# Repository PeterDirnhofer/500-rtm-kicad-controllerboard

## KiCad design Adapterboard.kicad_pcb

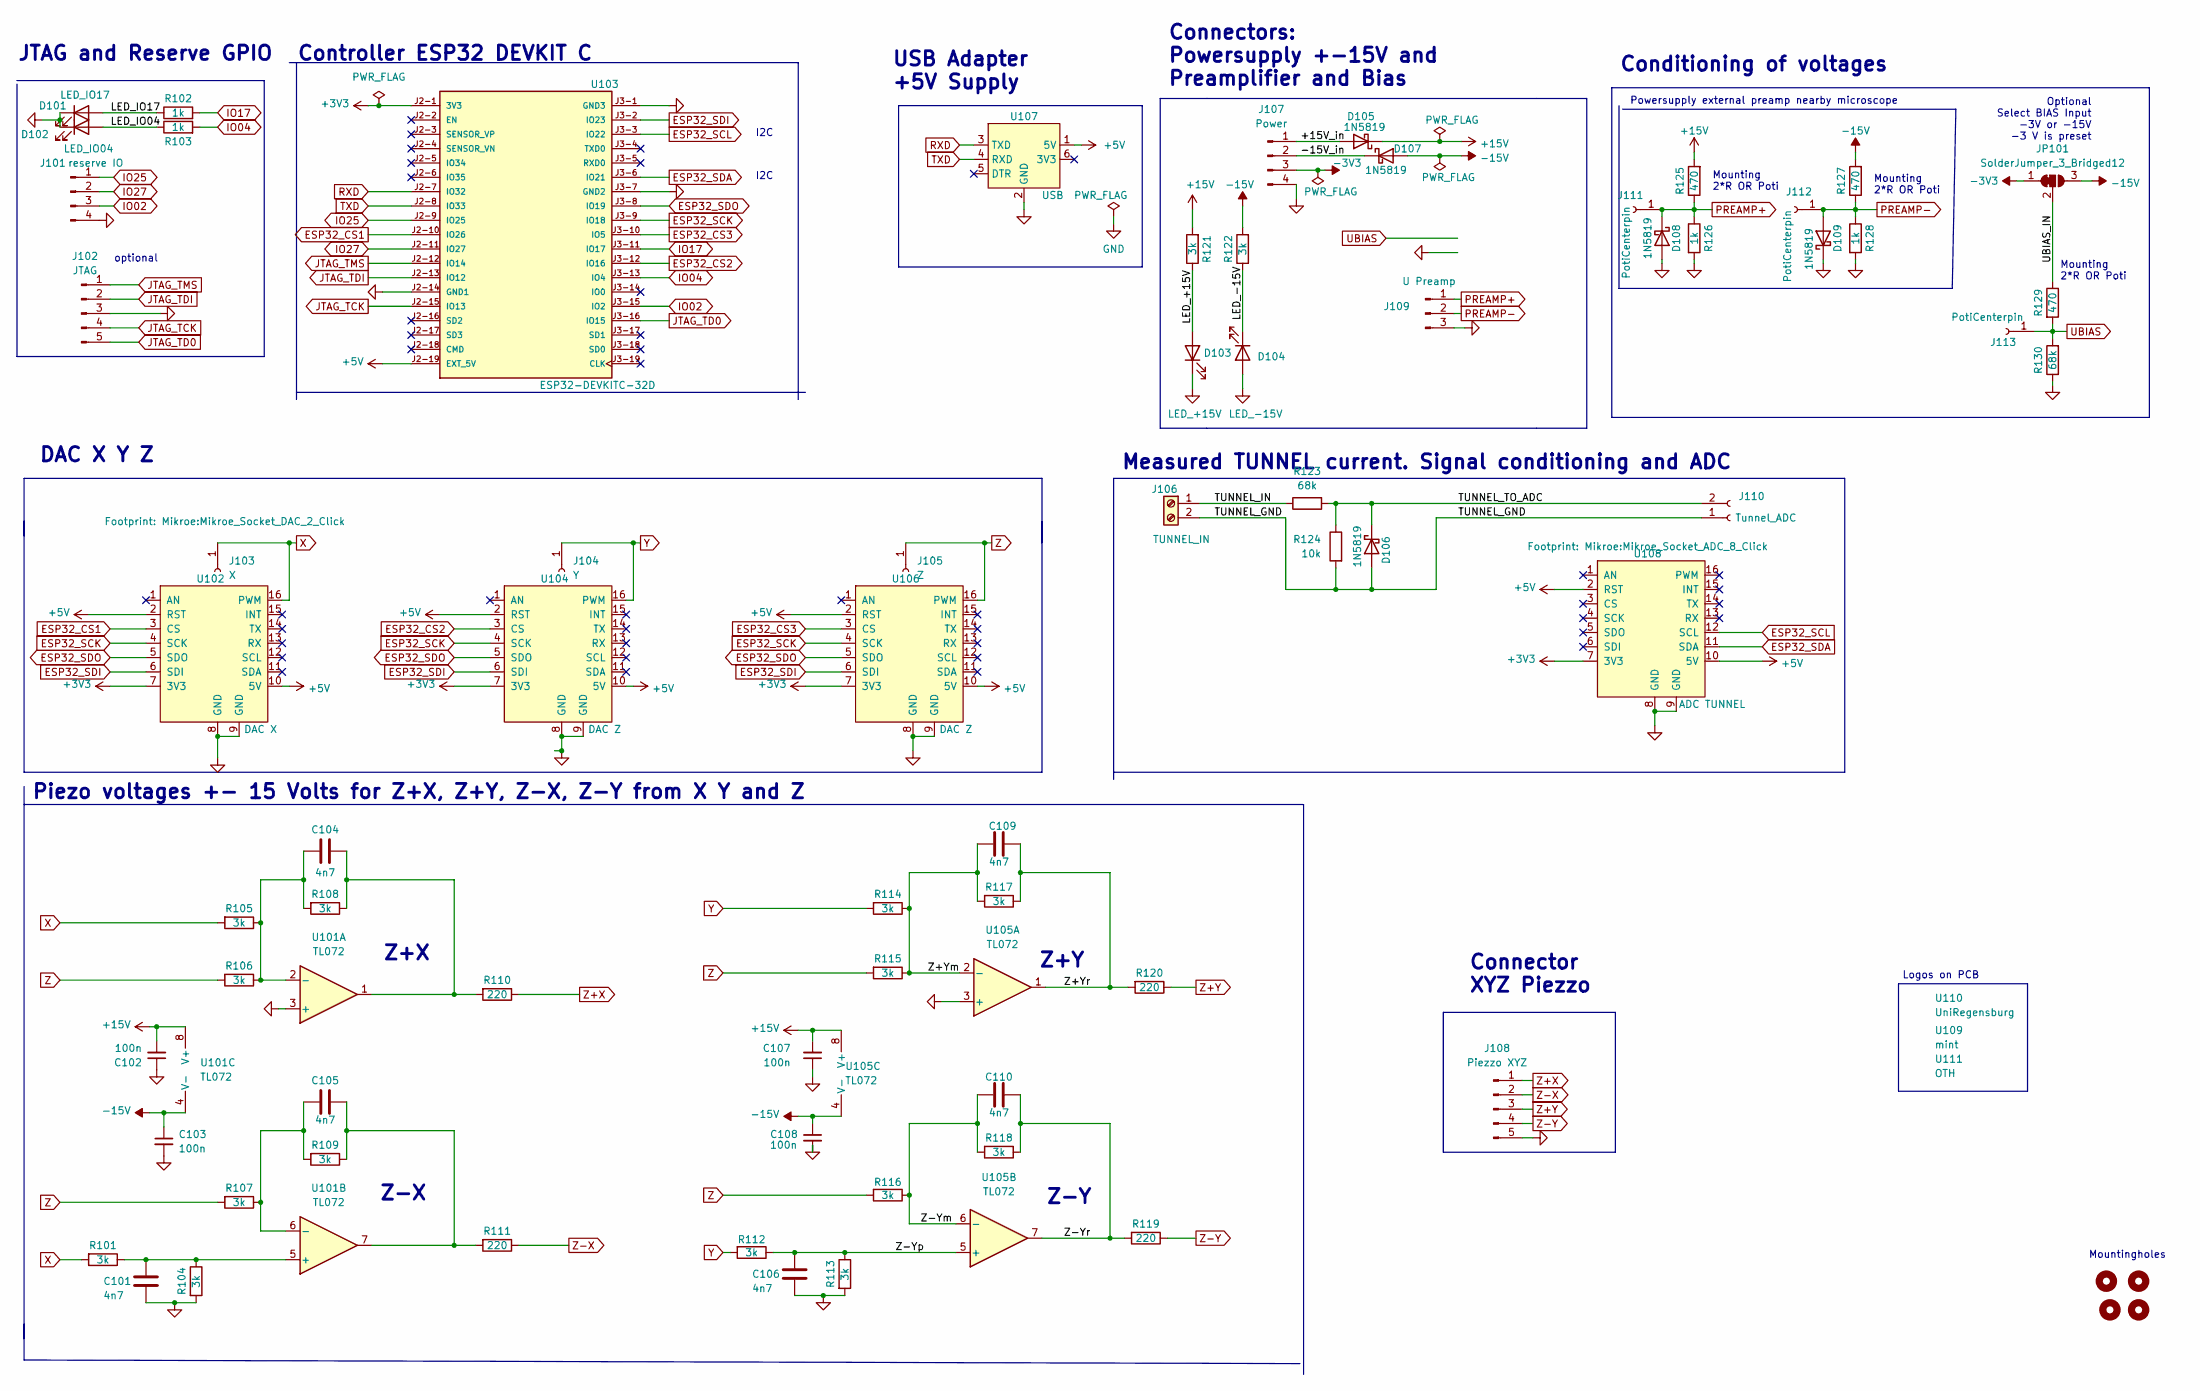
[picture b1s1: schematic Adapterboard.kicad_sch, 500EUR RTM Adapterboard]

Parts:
C101, C104, C105, C106, C109, C110: 4n7; C_Disc_D5.0mm_W2.5mm_P2.50mm
C102, C103, C107, C108: 100n; C_Disc_D5.0mm_W2.5mm_P2.50mm
D101: LED_IO17; LED_D3.0mm_Clear
D102: LED_IO04; LED_D3.0mm_Clear
D103: LED_+15V; LED_D3.0mm_Clear
D104: LED_-15V; LED_D3.0mm_Clear
D105, D106, D107, D108, D109: 1N5819; D_DO-41_SOD81_P10.16mm_Horizontal
H101, H102, H103, H104: MountingHole; MountingHole_3.2mm_M3
J101: reserve IO; PinHeader_1x04_P2.54mm_Vertical
J102: JTAG; PinHeader_1x05_P2.54mm_Vertical
J103: X; PinHeader_1x01_P2.54mm_Vertical
J104: Y; PinHeader_1x01_P2.54mm_Vertical
J105: Z; PinHeader_1x01_P2.54mm_Vertical
J106: TUNNEL_IN; PinHeader_1x02_P2.54mm_Vertical
J107: Power; PinHeader_1x04_P2.54mm_Vertical
J108: Piezzo XYZ; PinHeader_1x05_P2.54mm_Vertical
J109: U Preamp; PinHeader_1x03_P2.54mm_Vertical
J110: Tunnel_ADC; PinHeader_1x02_P2.54mm_Vertical
J111, J112, J113: PotiCenterpin; Poti_mid_contact
JP101: SolderJumper_3_Bridged12; SolderJumper-3_P1.3mm_Bridged12_RoundedPad1.0x1.5mm
R101, R104, R105, R106, R107, R108, R109, R112, R113, R114, R115, R116, R117, R118, R121, R122: 3k; R_Axial_DIN0207_L6.3mm_D2.5mm_P10.16mm_Horizontal
R102, R103, R126, R128: 1k; R_Axial_DIN0207_L6.3mm_D2.5mm_P10.16mm_Horizontal
R110, R111, R119, R120: 220; R_Axial_DIN0207_L6.3mm_D2.5mm_P10.16mm_Horizontal
R123, R130: 68k; R_Axial_DIN0207_L6.3mm_D2.5mm_P10.16mm_Horizontal
R124: 10k; R_Axial_DIN0207_L6.3mm_D2.5mm_P10.16mm_Horizontal
R125, R127, R129: 470; R_Axial_DIN0207_L6.3mm_D2.5mm_P10.16mm_Horizontal
U101, U105: TL072; DIP-8_W7.62mm
U102: DAC X; Mikroe_Socket_DAC_2_Click
U103: ESP32-DEVKITC-32D; MODULE_ESP32-DEVKITC-32D; PARTREV V4
U104, U106: DAC Z; Mikroe_Socket_DAC_2_Click
U107: USB; PinSocket_1x06_P2.54mm_Vertical
U108: ADC TUNNEL; Mikroe_Socket_ADC_8_Click
U109: mint
U110: UniRegensburg; ur
U111: OTH; oth

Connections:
+3V3: U102.7 (3V3), U103.J2-1 (3V3), U104.7 (3V3), U106.7 (3V3), U108.7 (3V3)
+5V: U102.2 (RST), U102.10 (5V), U103.J2-19 (EXT_5V), U104.2 (RST), U104.10 (5V), U106.2 (RST), U106.10 (5V), U107.1 (5V), U108.2 (RST), U108.10 (5V)
+15V: C102.2, C107.2, D105.1 (K), R121.2, R125.2, U101.8 (V+), U105.8 (V+)
-3V3: J107.3, JP101.1 (A)
-15V: C103.1, C108.1, D107.2 (A), JP101.3 (B), R122.2, R127.2, U101.4 (V-), U105.4 (V-)
/+15V_in: D105.2 (A), J107.1
/-15V_in: D107.1 (K), J107.2
/LED_+15V: D103.2 (A), R121.1
/LED_-15V: D104.1 (K), R122.1
/LED_IO04: D102.2 (A), R103.1
/LED_IO17: D101.2 (A), R102.1
/TUNNEL_GND: D106.2 (A), J106.2, J110.1, R124.2
/TUNNEL_IN: J106.1, R123.1
/TUNNEL_TO_ADC: D106.1 (K), J110.2, R123.2, R124.1
/UBIAS_IN: JP101.2 (C), R129.1
/Z+Ym: C109.2, R114.1, R115.1, R117.2, U105.2 (-)
/Z+Yr: C109.1, R117.1, R120.2, U105.1
/Z-Ym: C110.2, R116.1, R118.2, U105.6 (-)
/Z-Yp: C106.1, R112.1, R113.1, U105.5 (+)
/Z-Yr: C110.1, R118.1, R119.2, U105.7
ESP32_CS1: U102.3 (CS), U103.J2-10 (IO26)
ESP32_CS2: U103.J3-12 (IO16), U104.3 (CS)
ESP32_CS3: U103.J3-10 (IO5), U106.3 (CS)
ESP32_SCK: U102.4 (SCK), U103.J3-9 (IO18), U104.4 (SCK), U106.4 (SCK)
ESP32_SCL: U103.J3-3 (IO22), U108.12 (SCL)
ESP32_SDA: U103.J3-6 (IO21), U108.11 (SDA)
ESP32_SDI: U102.6 (SDI), U103.J3-2 (IO23), U104.6 (SDI), U106.6 (SDI)
ESP32_SDO: U102.5 (SDO), U103.J3-8 (IO19), U104.5 (SDO), U106.5 (SDO)
GND: C101.2, C102.1, C103.2, C106.2, C107.1, C108.2, D101.1 (K), D102.1 (K), D103.1 (K), D104.2 (A), D108.2 (A), D109.1 (K), J101.4, J102.3, J107.4, J108.5, J109.3, R104.2, R113.2, R126.2, R128.2, R130.1, U101.3 (+), U102.8 (GND), U102.9 (GND), U103.J2-14 (GND1), U103.J3-1 (GND3), U103.J3-7 (GND2), U104.8 (GND), U104.9 (GND), U105.3 (+), U106.8 (GND), U106.9 (GND), U107.2 (GND), U108.8 (GND), U108.9 (GND)
IO02: J101.3, U103.J3-15 (IO2)
IO04: R103.2, U103.J3-13 (IO4)
IO17: R102.2, U103.J3-11 (IO17)
IO25: J101.1, U103.J2-9 (IO25)
IO27: J101.2, U103.J2-11 (IO27)
JTAG_TCK: J102.4, U103.J2-15 (IO13)
JTAG_TD0: J102.5, U103.J3-16 (IO15)
JTAG_TDI: J102.2, U103.J2-13 (IO12)
JTAG_TMS: J102.1, U103.J2-12 (IO14)
unnamed: C104.1, R108.1, R110.2, U101.1
unnamed: C105.1, R109.1, R111.2, U101.7
unnamed: C104.2, R105.1, R106.1, R108.2, U101.2 (-)
unnamed: C101.1, R101.1, R104.1, U101.5 (+)
unnamed: C105.2, R107.1, R109.2, U101.6 (-)
PREAMP+: D108.1 (K), J109.1, J111.1, R125.1, R126.1
PREAMP-: D109.2 (A), J109.2, J112.1, R127.1, R128.1
RXD: U103.J2-7 (IO32), U107.3 (TXD)
TXD: U103.J2-8 (IO33), U107.4 (RXD)
UBIAS: J113.1, R129.2, R130.2
X: J103.1, R101.2, R105.2, U102.16 (PWM)
Y: J104.1, R112.2, R114.2, U104.16 (PWM)
Z: J105.1, R106.2, R107.2, R115.2, R116.2, U106.16 (PWM)
Z+X: J108.1, R110.1
Z+Y: J108.3, R120.1
Z-X: J108.2, R111.1
Z-Y: J108.4, R119.1

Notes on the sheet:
Measured TUNNEL current. Signal conditioning and ADC
Connector XYZ Piezzo
JTAG and Reserve GPIO
Mounting 2*R OR Poti
I2C
Z-Y
USB Adapter +5V Supply
optional
Connectors: Powersupply +-15V and Preamplifier and Bias
Controller ESP32 DEVKIT C
Mountingholes
Piezo voltages +- 15 Volts for Z+X, Z+Y, Z-X, Z-Y from X Y and Z
Logos on PCB
DAC X Y Z
Optional Select BIAS Input -3V or -15V -3 V is preset
Z-X
Powersupply external preamp nearby microscope
Z+X
Conditioning of voltages
Z+Y

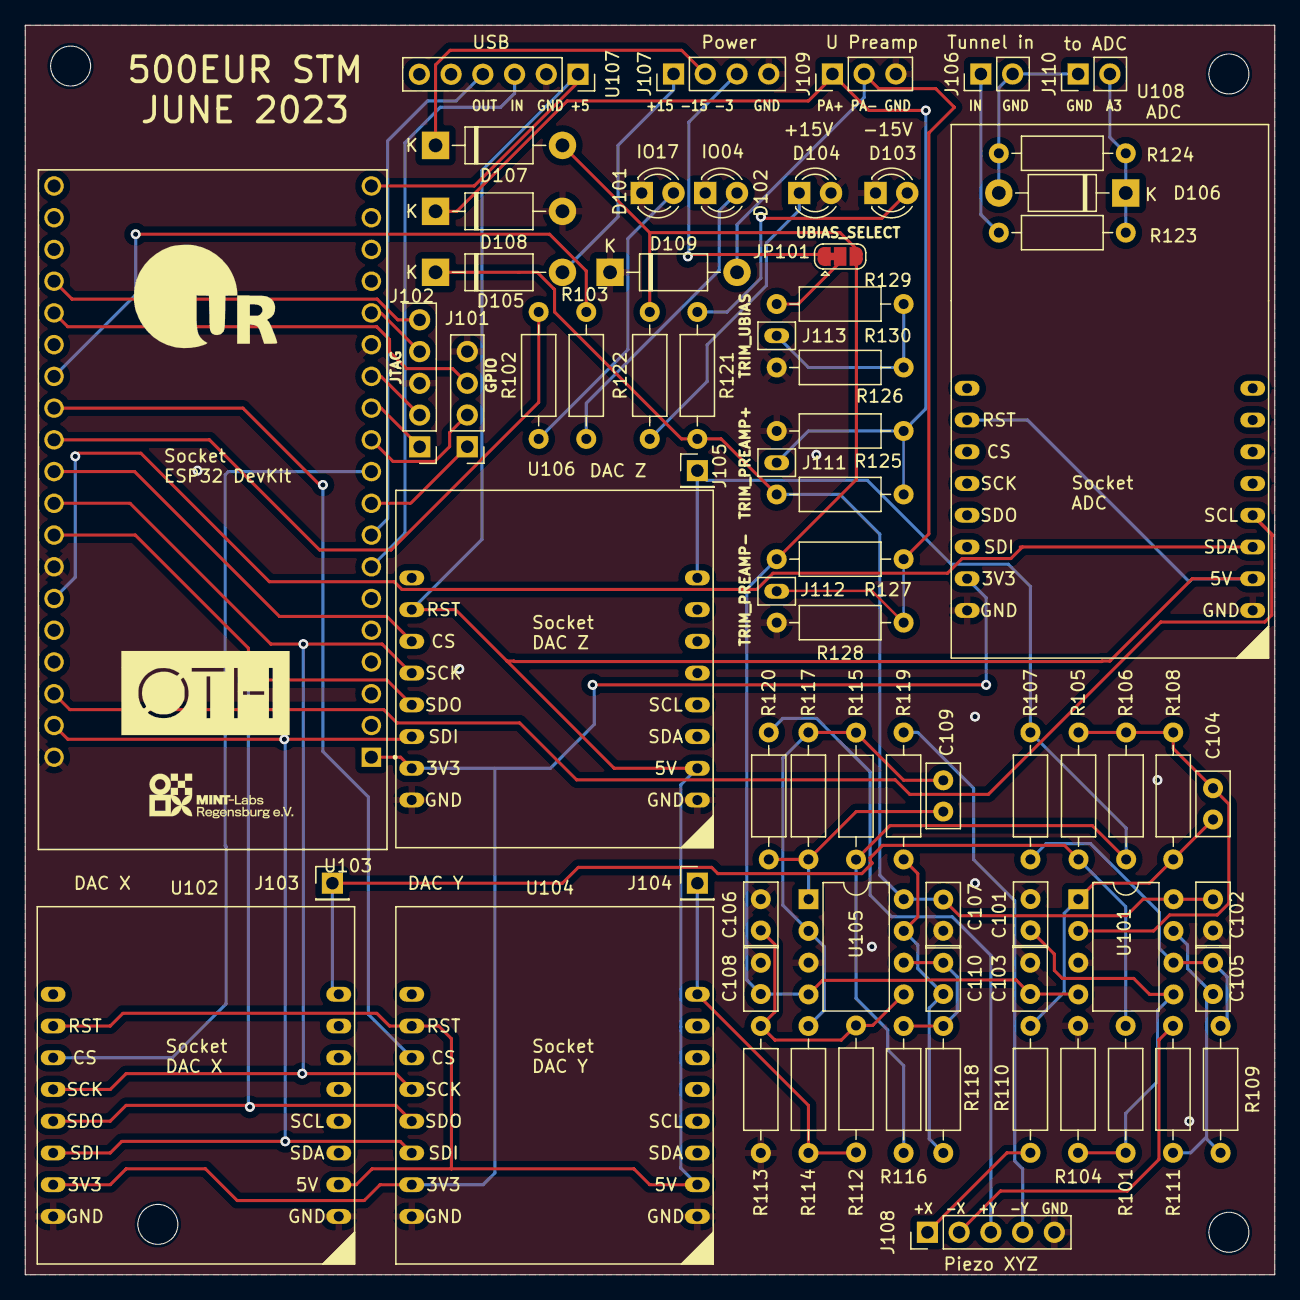
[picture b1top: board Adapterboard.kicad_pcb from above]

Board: 2 copper layers, 100.0 x 100.0 mm, 78 parts (0 on the bottom side), 55 nets.

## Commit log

2023-06-15 gitignore added
2023-06-16 brd and sch to ver7
2023-06-19 KiCad v7 update
2023-06-20 ESP 3D added
